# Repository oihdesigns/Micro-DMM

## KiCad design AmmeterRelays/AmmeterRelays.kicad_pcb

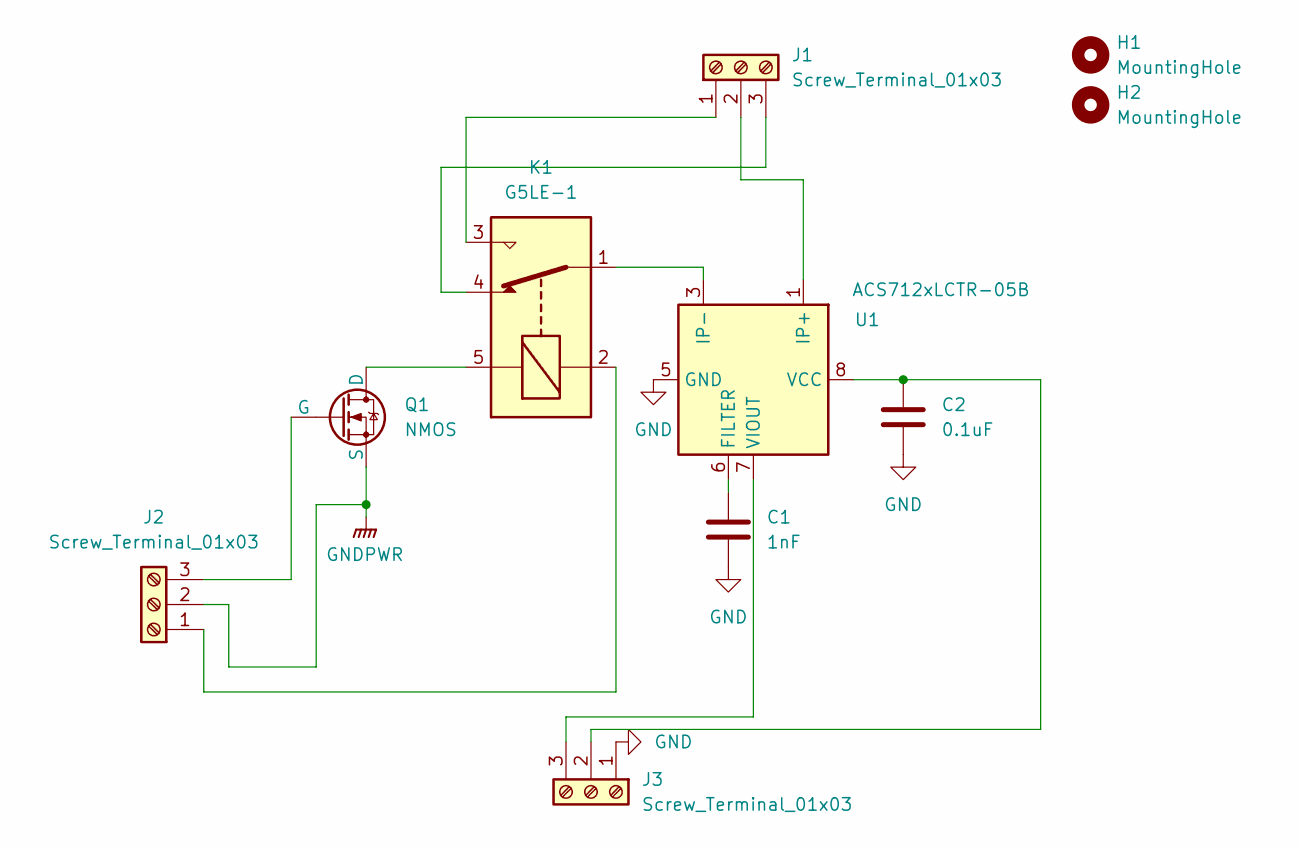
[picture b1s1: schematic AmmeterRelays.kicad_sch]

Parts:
C1: 1nF; C_0805_2012Metric_Pad1.18x1.45mm_HandSolder
C2: 0.1uF; C_0805_2012Metric_Pad1.18x1.45mm_HandSolder
H1, H2: MountingHole; MountingHole_3.2mm_M3_DIN965_Pad_TopBottom
J1: Screw_Terminal_01x03; TerminalBlock_CUI_TB007-508-03_1x03_P5.08mm_Horizontal
J2, J3: Screw_Terminal_01x03; PinSocket_1x03_P2.54mm_Vertical
K1: G5LE-1; Relay_SPDT_Omron-G5LE-1
Q1: NMOS; SOT-23-3
U1: ACS712xLCTR-05B; SOIC-8_3.9x4.9mm_P1.27mm

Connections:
GND: C1.2, C2.2, J3.1, U1.5 (GND)
GNDPWR: J2.2, Q1.2 (S)
unnamed: J1.1, K1.3
unnamed: J1.2, U1.1 (IP+), U1.2 (IP+)
unnamed: J1.3, K1.4
unnamed: J2.1, K1.2
unnamed: J2.3, Q1.1 (G)
unnamed: C2.1, J3.2, U1.8 (VCC)
unnamed: J3.3, U1.7 (VIOUT)
unnamed: K1.1, U1.3 (IP-), U1.4 (IP-)
unnamed: K1.5, Q1.3 (D)
unnamed: C1.1, U1.6 (FILTER)

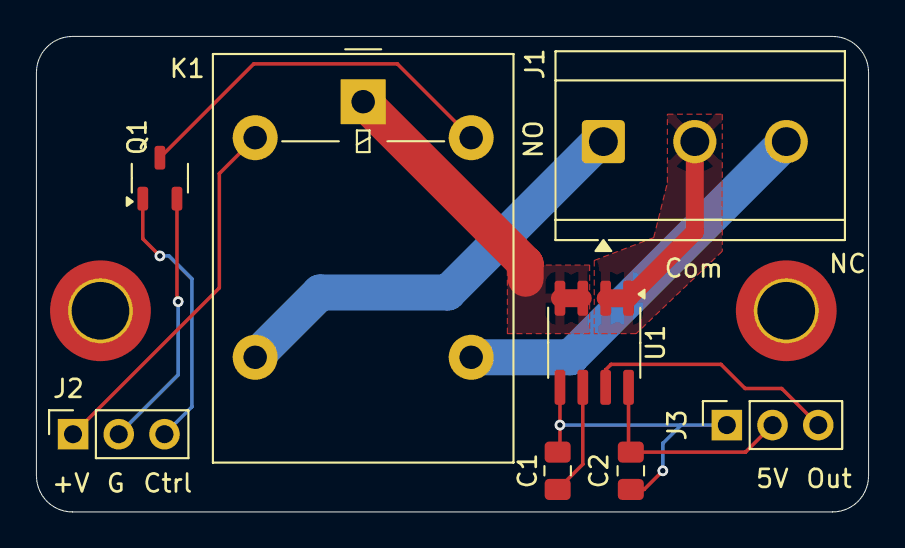
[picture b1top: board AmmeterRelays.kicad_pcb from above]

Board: 2 copper layers, 46.2 x 26.4 mm, 10 parts (0 on the bottom side), 12 nets.

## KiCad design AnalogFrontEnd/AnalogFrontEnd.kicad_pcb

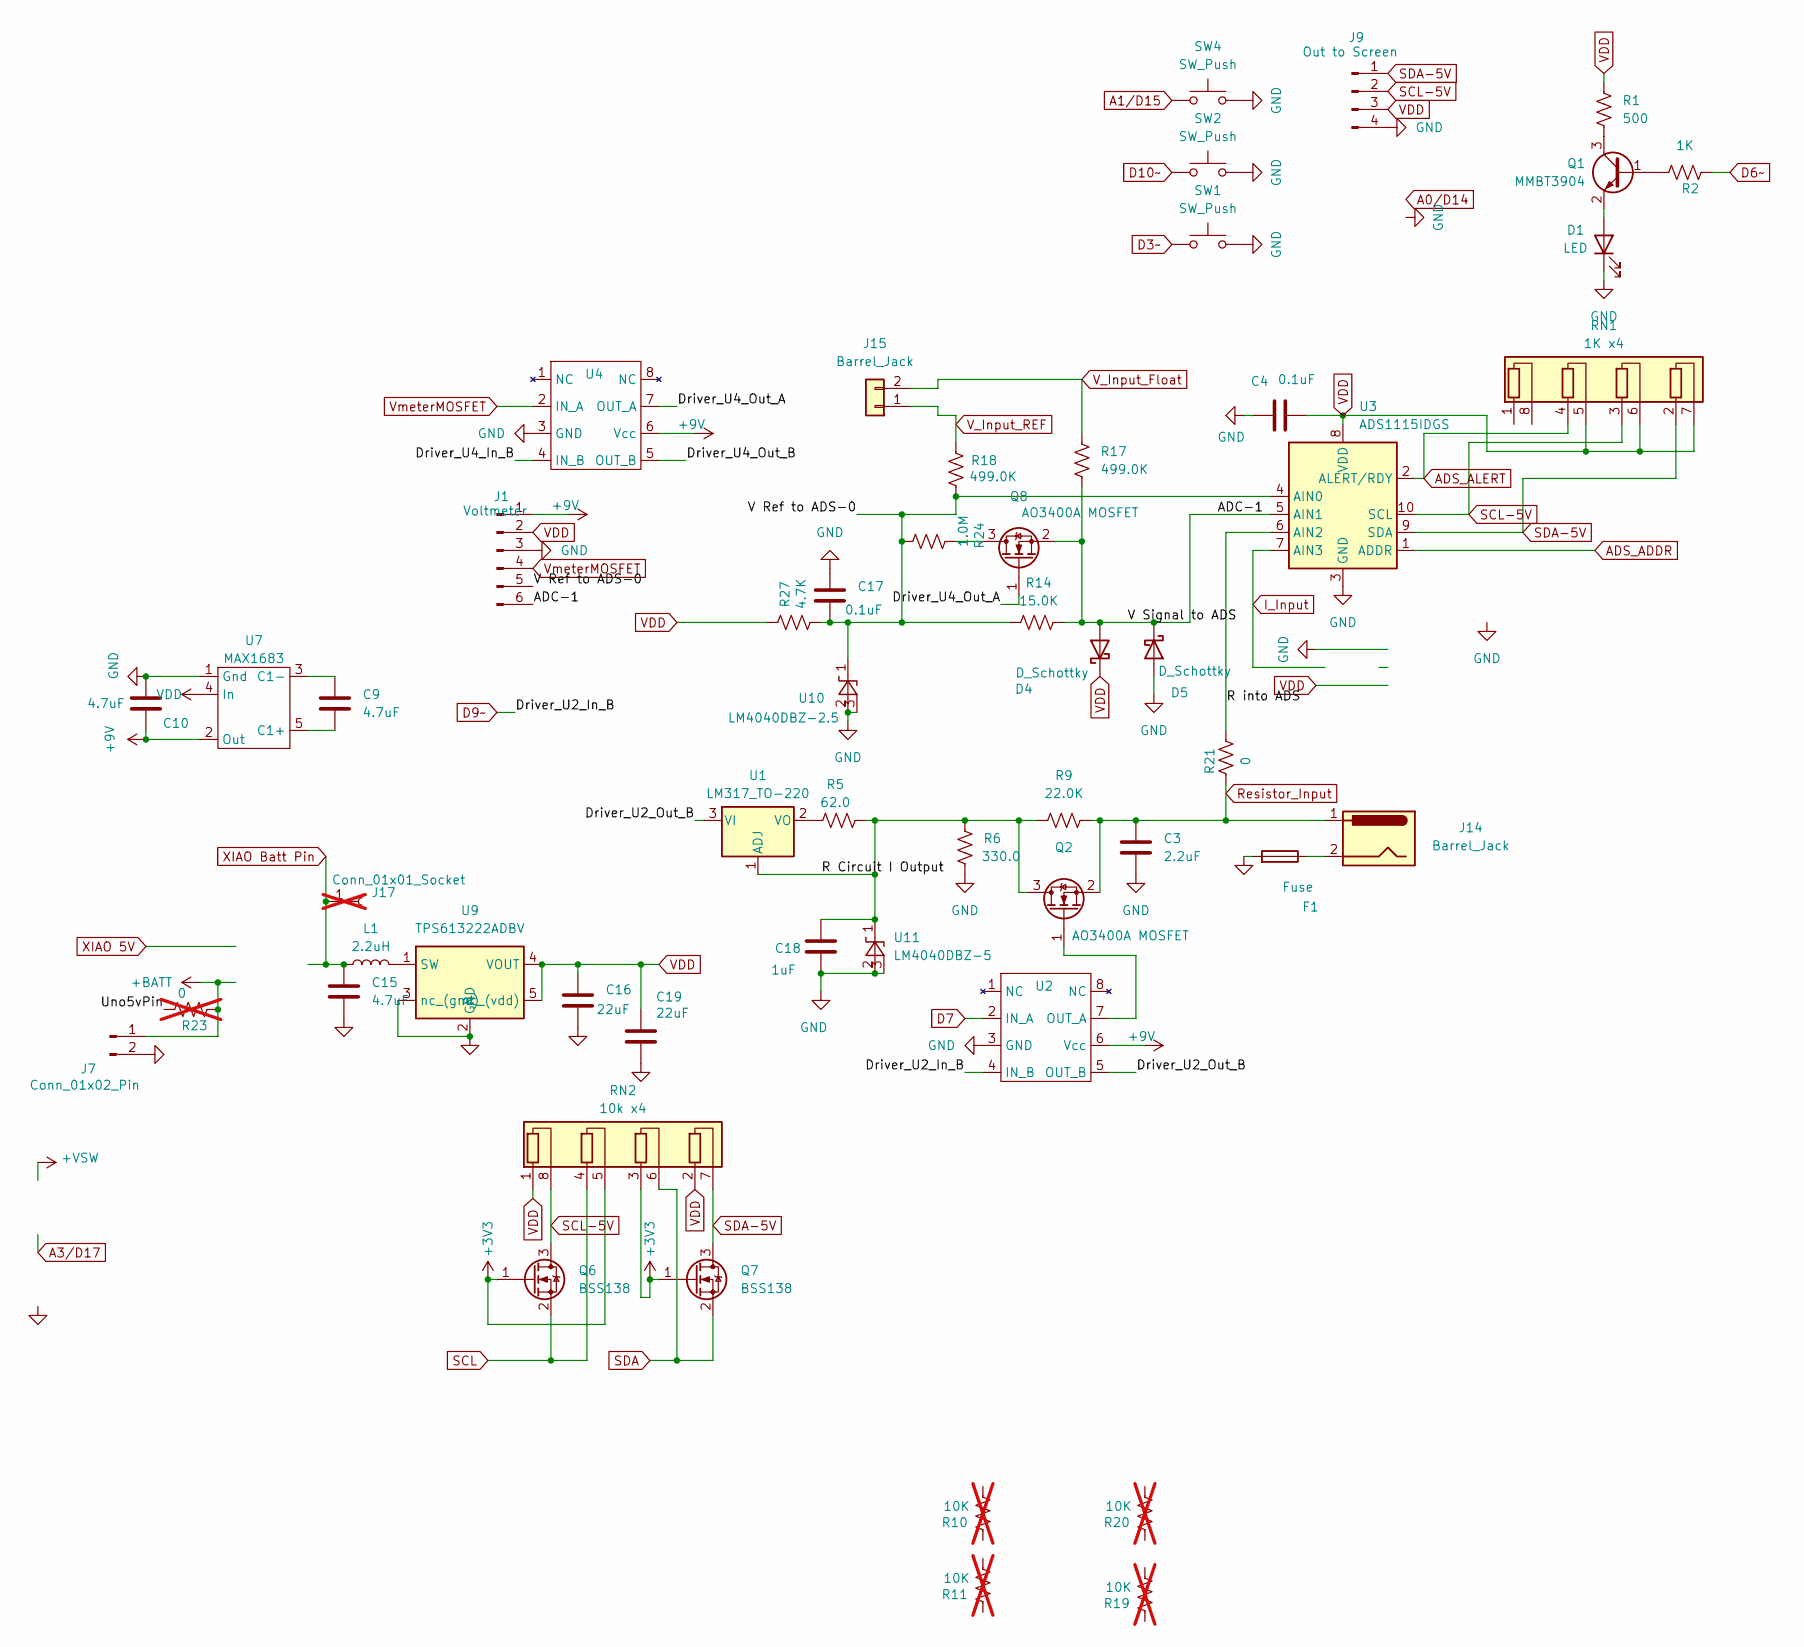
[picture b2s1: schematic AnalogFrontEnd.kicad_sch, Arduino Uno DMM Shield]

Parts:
C3: 2.2uF; C_0805_2012Metric_Pad1.18x1.45mm_HandSolder
C4, C17: 0.1uF; C_0805_2012Metric_Pad1.18x1.45mm_HandSolder
C9, C10, C15: 4.7uF; C_0805_2012Metric_Pad1.18x1.45mm_HandSolder
C16, C19: 22uF; C_0805_2012Metric_Pad1.18x1.45mm_HandSolder
C18: 1uF; C_0805_2012Metric_Pad1.18x1.45mm_HandSolder
D1: LED; LED_Luminus_MP-3030-1100_3.0x3.0mm
D4, D5: D_Schottky; D_SOD-123
F1: Fuse; Fuse_1206_3216Metric_Pad1.42x1.75mm_HandSolder
J1: Voltmeter; PinSocket_1x05_P2.54mm_Vertical
J7: Conn_01x02_Pin; PinSocket_1x02_P2.54mm_Vertical
J9: Out to Screen; PinSocket_1x04_P2.54mm_Vertical
J14: Barrel_Jack; BarrelJack_Horizontal
J15: Barrel_Jack; TerminalBlock_Phoenix_MKDS-3-2-5.08_1x02_P5.08mm_Horizontal
J17: Conn_01x01_Socket; PinSocket_1x01_P2.54mm_Vertical; not fitted
L1: 2.2uH; L_Murata_DFE201610P
Q1: MMBT3904; SOT-23
Q2, Q8: AO3400A MOSFET; SOT-23
Q6, Q7: BSS138; SOT-23
R1: 500; R_0805_2012Metric_Pad1.20x1.40mm_HandSolder
R2: 1K; R_0805_2012Metric_Pad1.20x1.40mm_HandSolder
R5: 62.0; R_0805_2012Metric_Pad1.20x1.40mm_HandSolder
R6: 330.0; R_0805_2012Metric_Pad1.20x1.40mm_HandSolder
R9: 22.0K; R_0805_2012Metric_Pad1.20x1.40mm_HandSolder
R10, R11, R19, R20: 10K; R_0805_2012Metric_Pad1.20x1.40mm_HandSolder; not fitted
R14: 15.0K; R_0805_2012Metric_Pad1.20x1.40mm_HandSolder
R17, R18: 499.0K; R_0805_2012Metric_Pad1.20x1.40mm_HandSolder
R21: 0; R_0805_2012Metric_Pad1.20x1.40mm_HandSolder
R23: 0; R_0805_2012Metric_Pad1.20x1.40mm_HandSolder; not fitted
R24: 1.0M; R_0805_2012Metric_Pad1.20x1.40mm_HandSolder
R27: 4.7K; R_0805_2012Metric_Pad1.20x1.40mm_HandSolder
RN1: 1K x4; RESCAXS127P508X320X70-8N
RN2: 10k x4; RESCAXS127P508X320X70-8N
SW1, SW2, SW4: SW_Push; SW_SPST_CK_RS282G05A3
U1: LM317_TO-220; SOT-223-3_TabPin2
U2, U4: IX4426N; SOIC-8_3.9x4.9mm_P1.27mm
U3: ADS1115IDGS; TSSOP-10_3x3mm_P0.5mm
U7: MAX1683; SOT-23-5_HandSoldering
U9: TPS613222ADBV; SOT-23-5
U10: LM4040DBZ-2.5; SOT-23
U11: LM4040DBZ-5; SOT-23

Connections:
+3V3: Q6.1 (G), Q7.1 (G), RN2.3 (R3.1), RN2.5 (R2.2)
+9V: C10.2, J1.1, U2.6 (Vcc), U4.6 (Vcc), U7.2 (Out)
+BATT: J7.1, R23.2
/ADC-1: D4.2 (A), D5.1 (K), J1.6, Q8.2 (S), R14.2, R17.2, U3.5 (AIN1)
/Driver_U2_Out_B: U1.3 (VI), U2.5 (OUT_B)
/Driver_U4_In_B: U4.4 (IN_B)
/Driver_U4_Out_A: Q8.1 (G), U4.7 (OUT_A)
/Driver_U4_Out_B: U4.5 (OUT_B)
/R Circuit I Output: C18.1, Q2.3 (D), R5.2, R6.2, R9.1, U1.1 (ADJ), U11.1 (K)
/R into ADS: R21.1, U3.6 (AIN2)
/Uno5vPin: R23.1
/V Ref to ADS-0: C17.2, J1.5, R14.1, R18.2, R24.2, R27.2, U3.4 (AIN0), U10.1 (K)
A1/D15: SW4.1
ADS_ADDR: U3.1 (ADDR)
ADS_ALERT: RN1.4 (R2.1), U3.2 (ALERT/RDY)
D3~: SW1.1
D6~: R2.1
D7: U2.2 (IN_A)
D9~: U2.4 (IN_B)
D10~: SW2.1
GND: C3.2, C4.1, C10.1, C15.2, C16.2, C17.1, C18.2, C19.2, D1.1 (K), D5.2 (A), F1.2, J1.3, J7.2, J9.4, R6.1, SW1.2, SW2.2, SW4.2, U2.3 (GND), U3.3 (GND), U4.3 (GND), U7.1 (Gnd), U9.2 (GND), U9.3 (nc_(gnd)), U10.2 (A), U10.3 (nc_(gnd)), U11.2 (A), U11.3 (nc_(gnd))
I_Input: U3.7 (AIN3)
unnamed: D1.2 (A), Q1.2 (E)
unnamed: F1.1, J14.2
unnamed: Q1.1 (B), R2.2
unnamed: Q1.3 (C), R1.1
unnamed: Q2.1 (G), U2.7 (OUT_A)
unnamed: Q8.3 (D), R24.1
unnamed: R5.1, U1.2 (VO)
unnamed: C9.2, U7.5 (C1+)
unnamed: C9.1, U7.3 (C1-)
unnamed: L1.2, U9.1 (SW)
Resistor_Input: C3.1, J14.1, Q2.2 (S), R9.2, R21.2
SCL: Q6.2 (S), RN2.4 (R2.1)
SCL-5V: J9.2, Q6.3 (D), RN1.3 (R3.1), RN2.8 (R1.2), U3.10 (SCL)
SDA: Q7.2 (S), RN2.6 (R3.2)
SDA-5V: J9.1, Q7.3 (D), RN1.2 (R4.1), RN2.7 (R4.2), U3.9 (SDA)
VDD: C4.2, C16.1, C19.1, D4.1 (K), J1.2, J9.3, R1.2, R27.1, RN1.5 (R2.2), RN1.6 (R3.2), RN1.7 (R4.2), RN2.1 (R1.1), RN2.2 (R4.1), U3.8 (VDD), U7.4 (In), U9.4 (VOUT), U9.5 (nc_(vdd))
V_Input_Float: J15.2, R17.1
V_Input_REF: J15.1, R18.1
VmeterMOSFET: J1.4, U4.2 (IN_A)
XIAO Batt Pin: C15.1, J17.1, L1.1

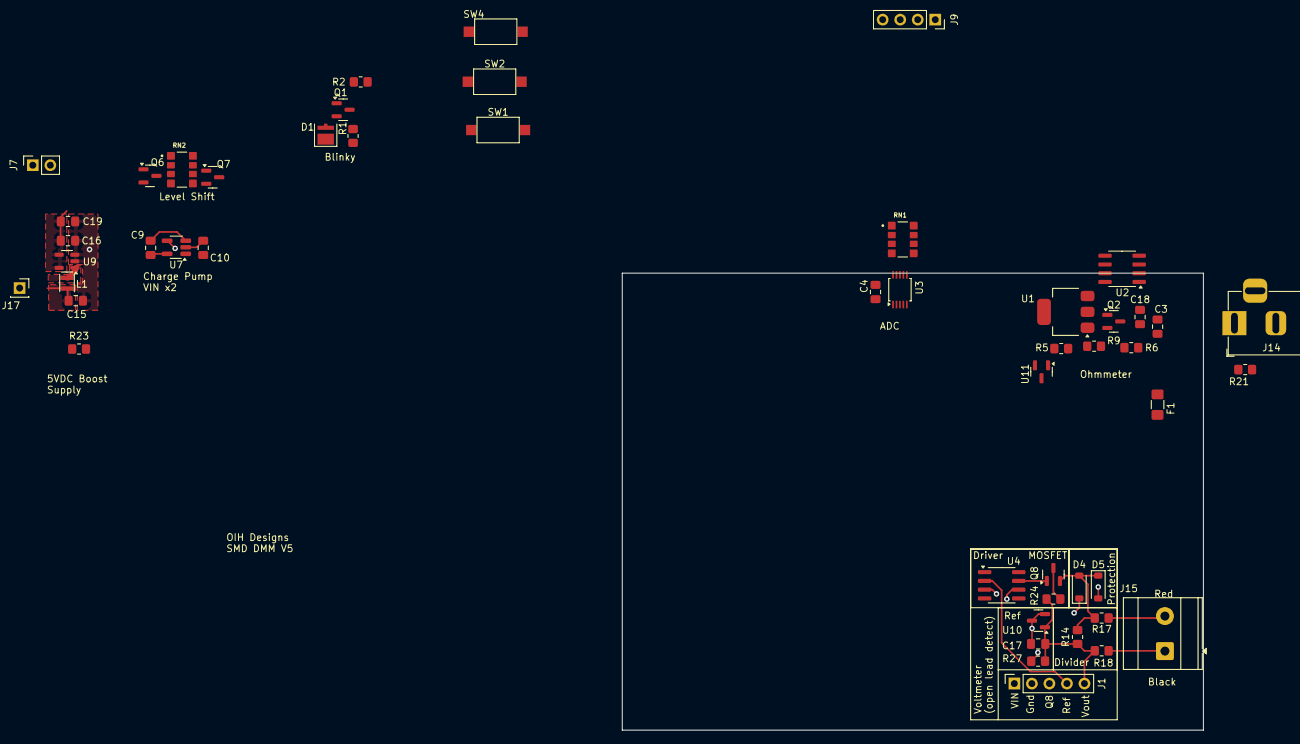
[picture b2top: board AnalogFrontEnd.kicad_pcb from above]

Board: 4 copper layers, 84.2 x 66.2 mm, 50 parts (0 on the bottom side), 31 nets.

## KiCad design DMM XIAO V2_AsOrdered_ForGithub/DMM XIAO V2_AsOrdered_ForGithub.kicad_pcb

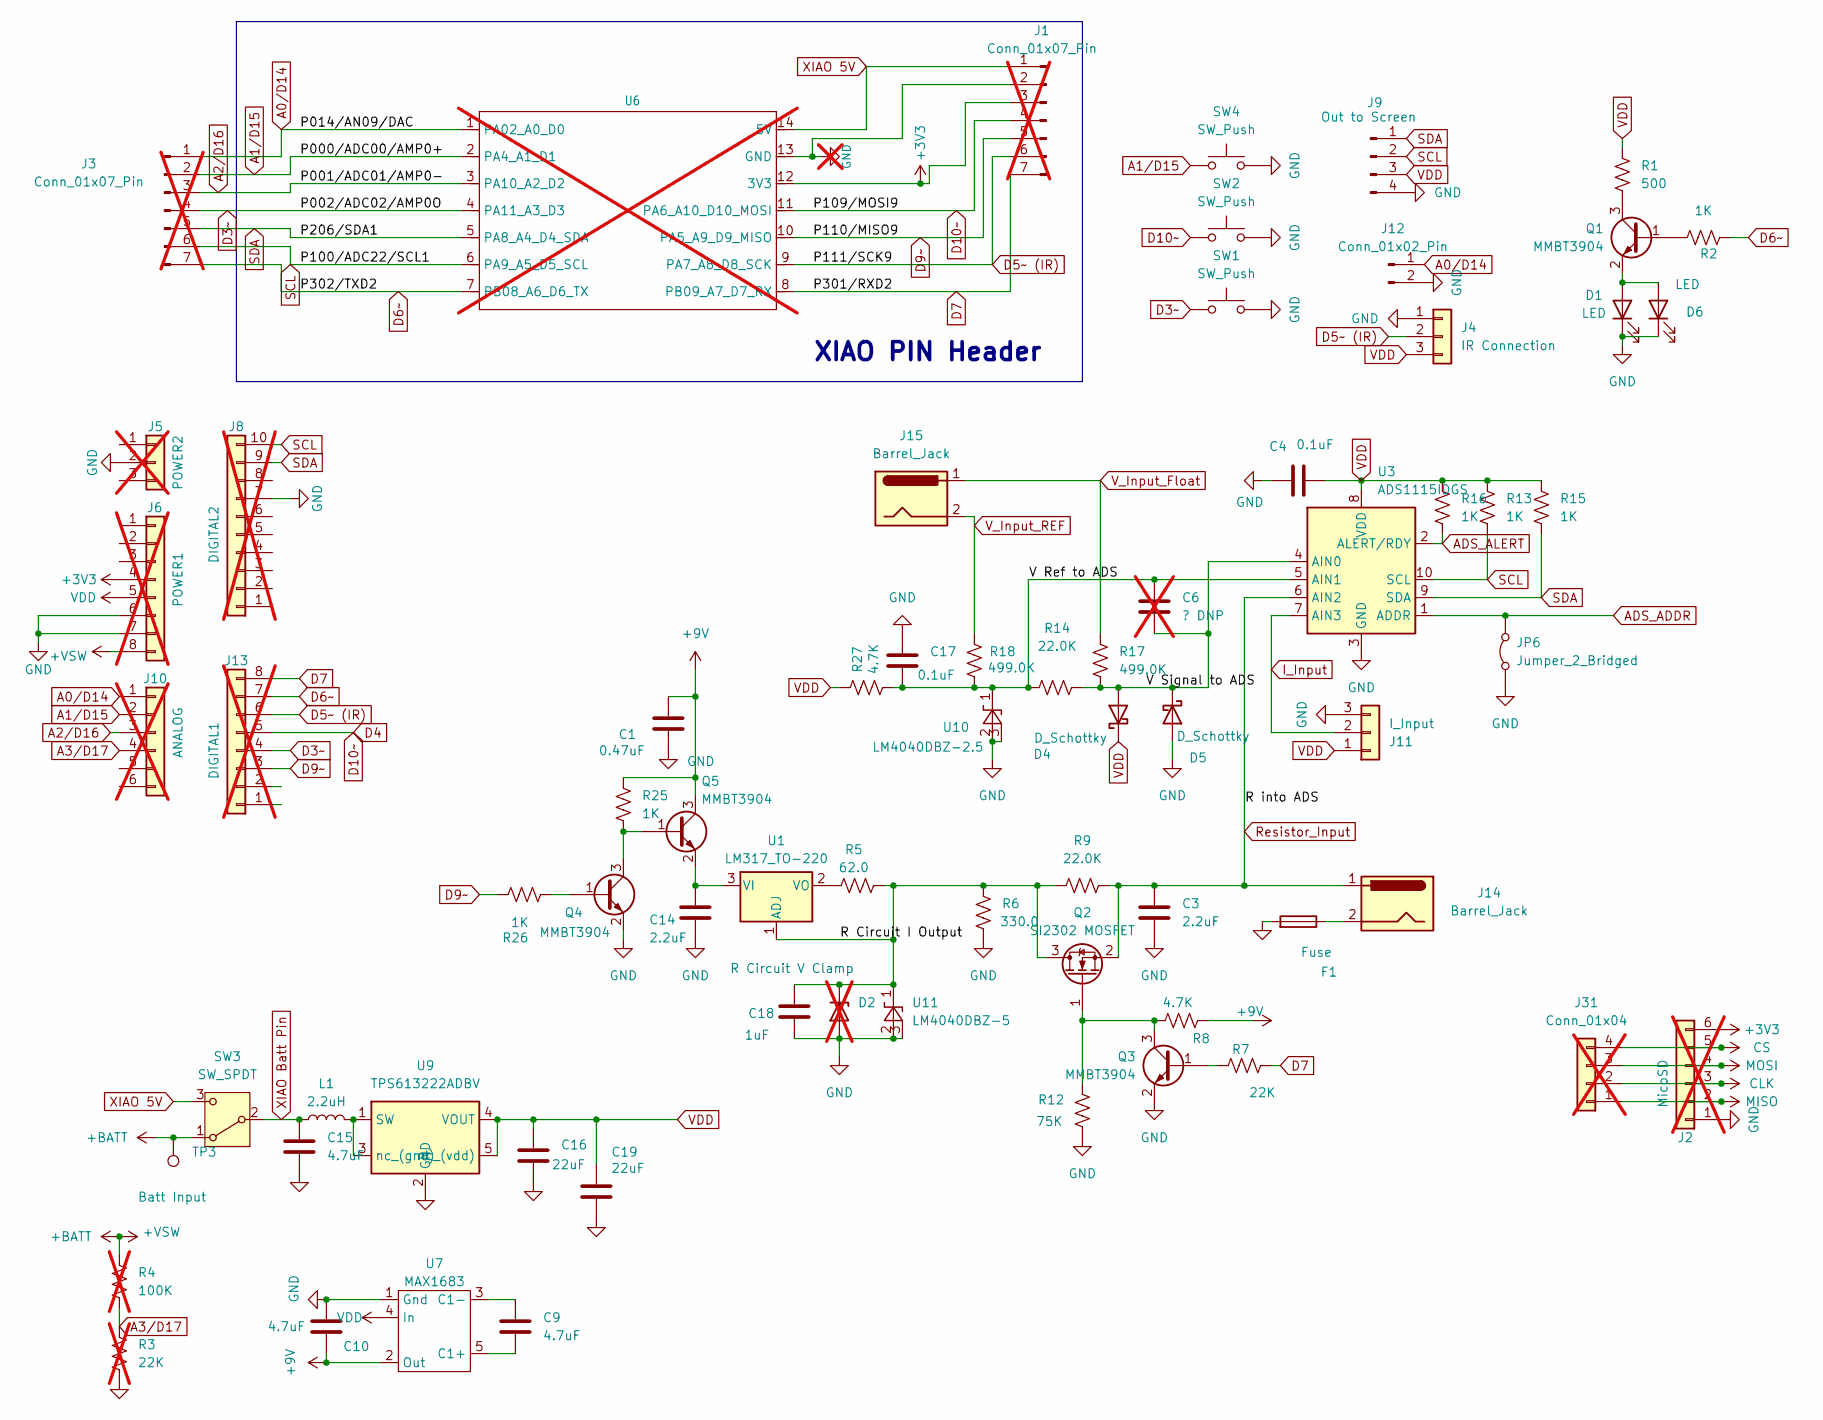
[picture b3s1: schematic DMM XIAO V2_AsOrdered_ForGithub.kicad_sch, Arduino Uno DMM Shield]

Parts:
C1: 0.47uF; C_0805_2012Metric_Pad1.18x1.45mm_HandSolder
C3, C14: 2.2uF; C_0805_2012Metric_Pad1.18x1.45mm_HandSolder
C4, C17: 0.1uF; C_0805_2012Metric_Pad1.18x1.45mm_HandSolder
C6: ? DNP; C_0805_2012Metric_Pad1.18x1.45mm_HandSolder; not fitted
C9, C10, C15: 4.7uF; C_0805_2012Metric_Pad1.18x1.45mm_HandSolder
C16, C19: 22uF; C_0805_2012Metric_Pad1.18x1.45mm_HandSolder
C18: 1uF; C_0805_2012Metric_Pad1.18x1.45mm_HandSolder
D1: LED; LED_Luminus_MP-3030-1100_3.0x3.0mm
D2: R Circuit V Clamp; D_SOD-123; not fitted
D4, D5: D_Schottky; D_SOD-123
D6: LED; LED_D3.0mm_Clear
F1: Fuse; Fuseholder_Clip-5x20mm_Keystone_3512P_Inline_P23.62x7.27mm_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
J1, J3: Conn_01x07_Pin; PinSocket_1x07_P2.54mm_Vertical; not fitted
J2: MicoSD; PinSocket_1x06_P2.54mm_Vertical; not fitted
J4: IR Connection; PinHeader_1x03_P2.54mm_Vertical_NoBox
J5: POWER2; PinHeader_1x03_P2.54mm_Vertical_NoBox; not fitted
J6: POWER1; PinHeader_1x08_P2.54mm_Vertical_NoBox; not fitted
J8: DIGITAL2; PinHeader_1x10_P2.54mm_Vertical_NoBox; not fitted
J9: Out to Screen; PinSocket_1x04_P2.54mm_Vertical
J10: ANALOG; PinHeader_1x06_P2.54mm_Vertical_NoBox; not fitted
J11: I_Input; PinHeader_1x03_P2.54mm_Horizontal
J12: Conn_01x02_Pin; PinHeader_1x02_P2.54mm_Horizontal
J13: DIGITAL1; PinHeader_1x08_P2.54mm_Vertical_NoBox; not fitted
J14, J15: Barrel_Jack; BarrelJack_Horizontal
J31: Conn_01x04; PinHeader_1x04_P2.54mm_Vertical; not fitted
JP6: Jumper_2_Bridged; SolderJumper-2_P1.3mm_Bridged_Pad1.0x1.5mm
L1: 2.2uH; L_Murata_DFE201610P
Q1, Q3, Q4, Q5: MMBT3904; SOT-23
Q2: SI2302 MOSFET; SOT-23
R1: 500; R_0805_2012Metric_Pad1.20x1.40mm_HandSolder
R2, R13, R15, R16, R25, R26: 1K; R_0805_2012Metric_Pad1.20x1.40mm_HandSolder
R3: 22K; R_0805_2012Metric_Pad1.20x1.40mm_HandSolder; not fitted
R4: 100K; R_0805_2012Metric_Pad1.20x1.40mm_HandSolder; not fitted
R5: 62.0; R_0805_2012Metric_Pad1.20x1.40mm_HandSolder
R6: 330.0; R_0805_2012Metric_Pad1.20x1.40mm_HandSolder
R7: 22K; R_0805_2012Metric_Pad1.20x1.40mm_HandSolder
R8, R27: 4.7K; R_0805_2012Metric_Pad1.20x1.40mm_HandSolder
R9, R14: 22.0K; R_0805_2012Metric_Pad1.20x1.40mm_HandSolder
R12: 75K; R_0805_2012Metric_Pad1.20x1.40mm_HandSolder
R17, R18: 499.0K; R_0805_2012Metric_Pad1.20x1.40mm_HandSolder
SW1, SW2: SW_Push; SW_PUSH_6mm
SW3: SW_SPDT; SW_Slide_SPDT_Angled_CK_OS102011MA1Q
SW4: SW_Push; SW_SPST_CK_RS282G05A3
TP3: Batt Input; PinHeader_1x01_P2.54mm_Vertical
U1: LM317_TO-220; SOT-223-3_TabPin2
U3: ADS1115IDGS; TSSOP-10_3x3mm_P0.5mm
U6: not fitted
U7: MAX1683; SOT-23-5_HandSoldering
U9: TPS613222ADBV; SOT-23-5
U10: LM4040DBZ-2.5; SOT-23
U11: LM4040DBZ-5; SOT-23

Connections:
+3V3: J1.3, J2.6, J6.4, U6.12 (3V3)
+9V: C1.1, C10.2, Q5.3 (C), R8.1, R25.2, U7.2 (Out)
+BATT: J6.8, R4.2, SW3.1 (A), TP3.1
/R Circuit I Output: C18.1, D2.1 (K), Q2.3 (D), R5.2, R6.2, R9.1, U1.1 (ADJ), U11.1 (K)
/V Ref to ADS: C6.1, C17.2, R14.1, R18.2, R27.2, U3.5 (AIN1), U10.1 (K)
/V Signal to ADS: C6.2, D4.2 (A), D5.1 (K), R14.2, R17.2, U3.4 (AIN0)
A0/D14: J3.1, J10.1, J12.1, U6.1 (PA02_A0_D0)
A1/D15: J3.2, J10.2, SW4.1, U6.2 (PA4_A1_D1)
A2/D16: J3.3, J10.3, U6.3 (PA10_A2_D2)
A3/D17: J10.4, R3.2, R4.1
ADS_ADDR: JP6.2 (B), U3.1 (ADDR)
ADS_ALERT: R16.1, U3.2 (ALERT/RDY)
CLK: J2.3, J31.2
CS: J2.5, J31.4
D3~: J3.4, J13.4, SW1.1, U6.4 (PA11_A3_D3)
D5~ (IR): J1.6, J4.2, J13.6, U6.9 (PA7_A8_D8_SCK)
D6~: J3.7, J13.7, R2.1, U6.7 (PB08_A6_D6_TX)
D7: J1.7, J13.8, R7.1, U6.8 (PB09_A7_D7_RX)
D9~: J1.5, J13.3, R26.2, U6.10 (PA5_A9_D9_MISO)
D10~: J1.4, J13.5, SW2.1, U6.11 (PA6_A10_D10_MOSI)
GND: C1.2, C3.2, C4.1, C10.1, C14.2, C15.2, C16.2, C17.1, C18.2, C19.2, D1.1 (K), D2.2 (A), D5.2 (A), D6.1 (K), F1.2, J1.2, J2.1, J4.1, J5.2, J6.6, J6.7, J8.7, J9.4, J11.3, J12.2, JP6.1 (A), Q3.2 (E), Q4.2 (E), R3.1, R6.1, R12.1, SW1.2, SW2.2, SW4.2, U3.3 (GND), U6.13 (GND), U7.1 (Gnd), U9.2 (GND), U10.2 (A), U10.3 (nc_(gnd)), U11.2 (A), U11.3 (nc_(gnd))
I_Input: J11.2, U3.7 (AIN3)
MISO: J2.2, J31.1
MOSI: J2.4, J31.3
unnamed: D1.2 (A), D6.2 (A), Q1.2 (E)
unnamed: F1.1, J14.2
unnamed: Q1.1 (B), R2.2
unnamed: Q1.3 (C), R1.1
unnamed: Q2.1 (G), Q3.3 (C), R8.2, R12.2
unnamed: Q3.1 (B), R7.2
unnamed: Q4.1 (B), R26.1
unnamed: Q4.3 (C), Q5.1 (B), R25.1
unnamed: C14.1, Q5.2 (E), U1.3 (VI)
unnamed: R5.1, U1.2 (VO)
unnamed: C9.2, U7.5 (C1+)
unnamed: C9.1, U7.3 (C1-)
unnamed: L1.2, U9.1 (SW), U9.3 (nc_(gnd))
Resistor_Input: C3.1, J14.1, Q2.2 (S), R9.2, U3.6 (AIN2)
SCL: J3.6, J8.10, J9.2, R13.1, U3.10 (SCL), U6.6 (PA9_A5_D5_SCL)
SDA: J3.5, J8.9, J9.1, R15.1, U3.9 (SDA), U6.5 (PA8_A4_D4_SDA)
VDD: C4.2, C16.1, C19.1, D4.1 (K), J4.3, J6.5, J9.3, J11.1, R1.2, R13.2, R15.2, R16.2, R27.1, U3.8 (VDD), U7.4 (In), U9.4 (VOUT), U9.5 (nc_(vdd))
V_Input_Float: J15.1, R17.1
V_Input_REF: J15.2, R18.1
XIAO 5V: J1.1, SW3.3 (C), U6.14 (5V)
XIAO Batt Pin: C15.1, L1.1, SW3.2 (B)

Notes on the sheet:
XIAO PIN Header

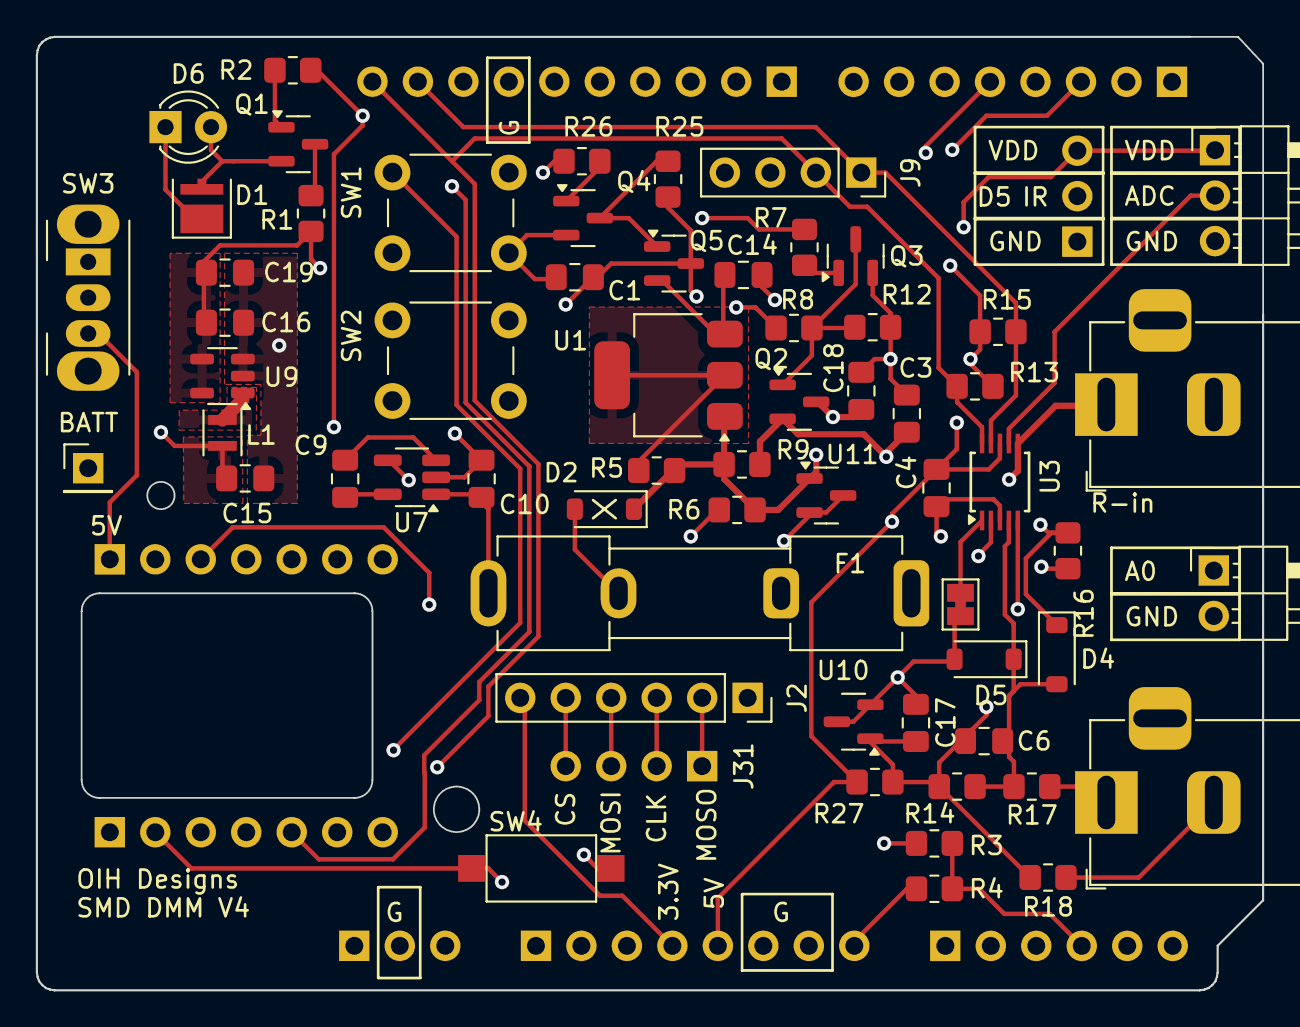
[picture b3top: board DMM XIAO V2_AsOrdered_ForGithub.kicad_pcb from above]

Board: 4 copper layers, 68.5 x 53.2 mm, 70 parts (0 on the bottom side), 45 nets.

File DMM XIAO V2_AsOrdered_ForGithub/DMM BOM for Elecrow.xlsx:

Reference | Value | Original | Footprint | Qty | Description | Purchase Link
C1 | 0.47uF | N | Capacitor_SMD:C_0805_2012Metric_Pad1.18x1.45mm_HandSolder | 1 | Unpolarized capacitor | https://www.digikey.com/en/products/detail/murata-electronic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
C16,C19 | 22uF | N | Capacitor_SMD:C_0805_2012Metric_Pad1.18x1.45mm_HandSolder | 2 | Unpolarized capacitor | https://www.digikey.com/en/products/detail/samsung-electro-m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
C18 | 1uF | N | Capacitor_SMD:C_0805_2012Metric_Pad1.18x1.45mm_HandSolder | 1 | Unpolarized capacitor | https://www.digikey.com/en/products/detail/samsung-electro-m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
C3,C14 | 2.2uF | N | Capacitor_SMD:C_0805_2012Metric_Pad1.18x1.45mm_HandSolder | 2 | Unpolarized capacitor | https://www.digikey.com/en/products/detail/samsung-electro-m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
C4,C17 | 0.1uF | N | Capacitor_SMD:C_0805_2012Metric_Pad1.18x1.45mm_HandSolder | 2 | Unpolarized capacitor | https://www.digikey.com/en/products/detail/samsung-electro-m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
C9,C10,C15 | 4.7uF | N | Capacitor_SMD:C_0805_2012Metric_Pad1.18x1.45mm_HandSolder | 3 | Unpolarized capacitor | https://www.digikey.com/en/products/detail/samsung-electro-m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
D1 | LED | Y | LED_SMD:LED_Luminus_MP-3030-1100_3.0x3.0mm | 1 | Light emitting diode | https://www.digikey.com/en/products/detail/luminus-devices-i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
D4,D5 | D_Schottky | N | Diode_SMD:D_SOD-123 | 2 | Schottky diode | https://www.digikey.com/en/products/detail/onsemi/BAT54T1G/918319
F1 | Fuse | N | Fuse:Fuseholder_Clip-5x20mm_Keystone_3512P_Inline_P23.62x7.27mm_D1.02x2.41x1.02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 | 2 | Fuse | https://www.digikey.com/en/products/detail/bel-fuse-inc/FC-2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
J11 | I_Input | N | Connector_PinHeader_2.54mm:PinHeader_1x03_P2.54mm_Horizontal | 1 | Generic connector, single row, 01x03, script generated (kicad-library-utils/sch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 | https://www.amazon.com/Chanzon-Straight-Connector-Breadboard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
J12 | Conn_01x02_Pin | N | Connector_PinHeader_2.54mm:PinHeader_1x02_P2.54mm_Horizontal | 1 | Generic connector, single row, 01x02, script generated | https://www.amazon.com/Chanzon-Straight-Connector-Breadboard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
J14,J15 | Barrel_Jack | N | Connector_BarrelJack:BarrelJack_Horizontal | 2 | DC Barrel Jack | https://www.amazon.com/California-JOS-Breadboard-Friendly-Mo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
J4 | IR Connection | N | Library:PinHeader_1x03_P2.54mm_Vertical_NoBox | 1 | Generic connector, single row, 01x03, script generated (kicad-library-utils/sch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 | https://www.amazon.com/Chanzon-Straight-Connector-Breadboard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
J9 | Out to Screen | N | Connector_PinSocket_2.54mm:PinSocket_1x04_P2.54mm_Vertical | 1 | Generic connector, single row, 01x04, script generated | https://www.amazon.com/Chanzon-Straight-Connector-Breadboard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
L1 | 2.2uH | N | Inductor_SMD:L_Murata_DFE201610P | 1 | Inductor | https://www.digikey.com/en/products/detail/murata-electronic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
Q1,Q3,Q4,Q5 | MMBT3904 | Y | Package_TO_SOT_SMD:SOT-23 | 4 | 0.2A Ic, 40V Vce, Small Signal NPN Transistor, SOT-23 | https://www.digikey.com/en/products/detail/diotec-semiconduc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
Q2 | SI2302 MOSFET | Y | Package_TO_SOT_SMD:SOT-23 | 1 | 4.2A Id, 20V Vds, N-Channel MOSFET, SOT-23 | https://www.digikey.com/en/products/detail/mcc-micro-commerc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
R1 | 500 | N | Resistor_SMD:R_0805_2012Metric_Pad1.20x1.40mm_HandSolder | 1 | Resistor, US symbol | https://www.digikey.com/en/products/detail/yageo/RC0805FR-07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
R12 | 100k | N | Resistor_SMD:R_0805_2012Metric_Pad1.20x1.40mm_HandSolder | 1 | Resistor, US symbol | https://www.digikey.com/en/products/detail/yageo/RC0805JR-07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
R17,R18 | 499.0K | Y | Resistor_SMD:R_0805_2012Metric_Pad1.20x1.40mm_HandSolder | 2 | Resistor, US symbol | https://www.digikey.com/en/products/detail/panasonic-electro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
R2,R13,R15,R16,R25,R26 | 1K | N | Resistor_SMD:R_0805_2012Metric_Pad1.20x1.40mm_HandSolder | 6 | Resistor, US symbol | https://www.digikey.com/en/products/detail/susumu/RR1220P-10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
R5 | 62 | Y | Resistor_SMD:R_0805_2012Metric_Pad1.20x1.40mm_HandSolder | 1 | Resistor, US symbol | https://www.digikey.com/en/products/detail/panasonic-electro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
R6 | 330 | Y | Resistor_SMD:R_0805_2012Metric_Pad1.20x1.40mm_HandSolder | 1 | Resistor, US symbol | https://www.digikey.com/en/products/detail/stackpole-electro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
R7, R8, R27 | 10K | N | Resistor_SMD:R_0805_2012Metric_Pad1.20x1.40mm_HandSolder | 3 | Resistor, US symbol | https://www.digikey.com/en/products/detail/yageo/RC0402JR-07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
R9,R14 | 22.0K | Y | Resistor_SMD:R_0805_2012Metric_Pad1.20x1.40mm_HandSolder | 2 | Resistor, US symbol | https://www.digikey.com/en/products/detail/susumu/RR1220P-22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
SW1,SW2 |  | N | Button_Switch_THT:SW_PUSH_6mm | 2 | Push button switch, generic, two pins | https://www.amazon.com/QTEATAK-Momentary-Tactile-Button-Swit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
SW3 | SW_SPDT | N | Button_Switch_THT:SW_Slide_SPDT_Angled_CK_OS102011MA1Q | 1 | Switch, single pole double throw | https://www.digikey.com/en/products/detail/c-k/OS102011MA1QN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
SW4 | SW_Push | N | SMD | 3 | Push button switch, generic, two pins | https://www.digikey.com/en/products/detail/c-k/PTS636SM43SMT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
U1 | LM317_TO-220 | Y | Package_TO_SOT_SMD:SOT-223-3_TabPin2 | 1 | 1.5A 35V Adjustable Linear Regulator, TO-220 | https://www.digikey.com/en/products/detail/texas-instruments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
U10 | LM4040DBZ-2.5 | Y | Package_TO_SOT_SMD:SOT-23 | 1 | 2.500V Precision Micropower Shunt Voltage Reference, SOT-23 | https://www.digikey.com/en/products/detail/texas-instruments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
U11 | LM4040DBZ-5 | Y | Package_TO_SOT_SMD:SOT-23 | 1 | 5.000V Precision Micropower Shunt Voltage Reference, SOT-23 | https://www.digikey.com/en/products/detail/texas-instruments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
U3 | ADS1115IDGS | Y | Package_SO:TSSOP-10_3x3mm_P0.5mm | 1 | Ultra-Small, Low-Power, I2C-Compatible, 860-SPS, 16-Bit ADCs With Internal Refe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 | https://www.digikey.com/en/products/detail/texas-instruments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
U7 | MAX1683 | Y | Package_TO_SOT_SMD:SOT-23-5_HandSoldering | 1 | IC REG CHARGE PUMP 2VIN SOT23-5 | https://www.digikey.com/en/products/detail/microchip-technol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
U9 | TPS613222ADBV | Y | Package_TO_SOT_SMD:SOT-23-5 | 1 | 1.8A Step-Up Converter, 5V Output Voltage, 0.9-5.5V Input Voltage, SOT-23-5 | https://www.digikey.com/en/products/detail/texas-instruments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
